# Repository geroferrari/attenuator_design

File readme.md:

Design a variable attenuator  from 0db to 30db  (steps of 1db) 

Max Frequency: 3GHz 

Max input Power: 0 dbm

Zin = Zout = 50 ohms.

Tools:
 - Jupyter notebooks
 - Qucs
 - Kicad
 
TO DO:
- finish design
- Assemble the pcb

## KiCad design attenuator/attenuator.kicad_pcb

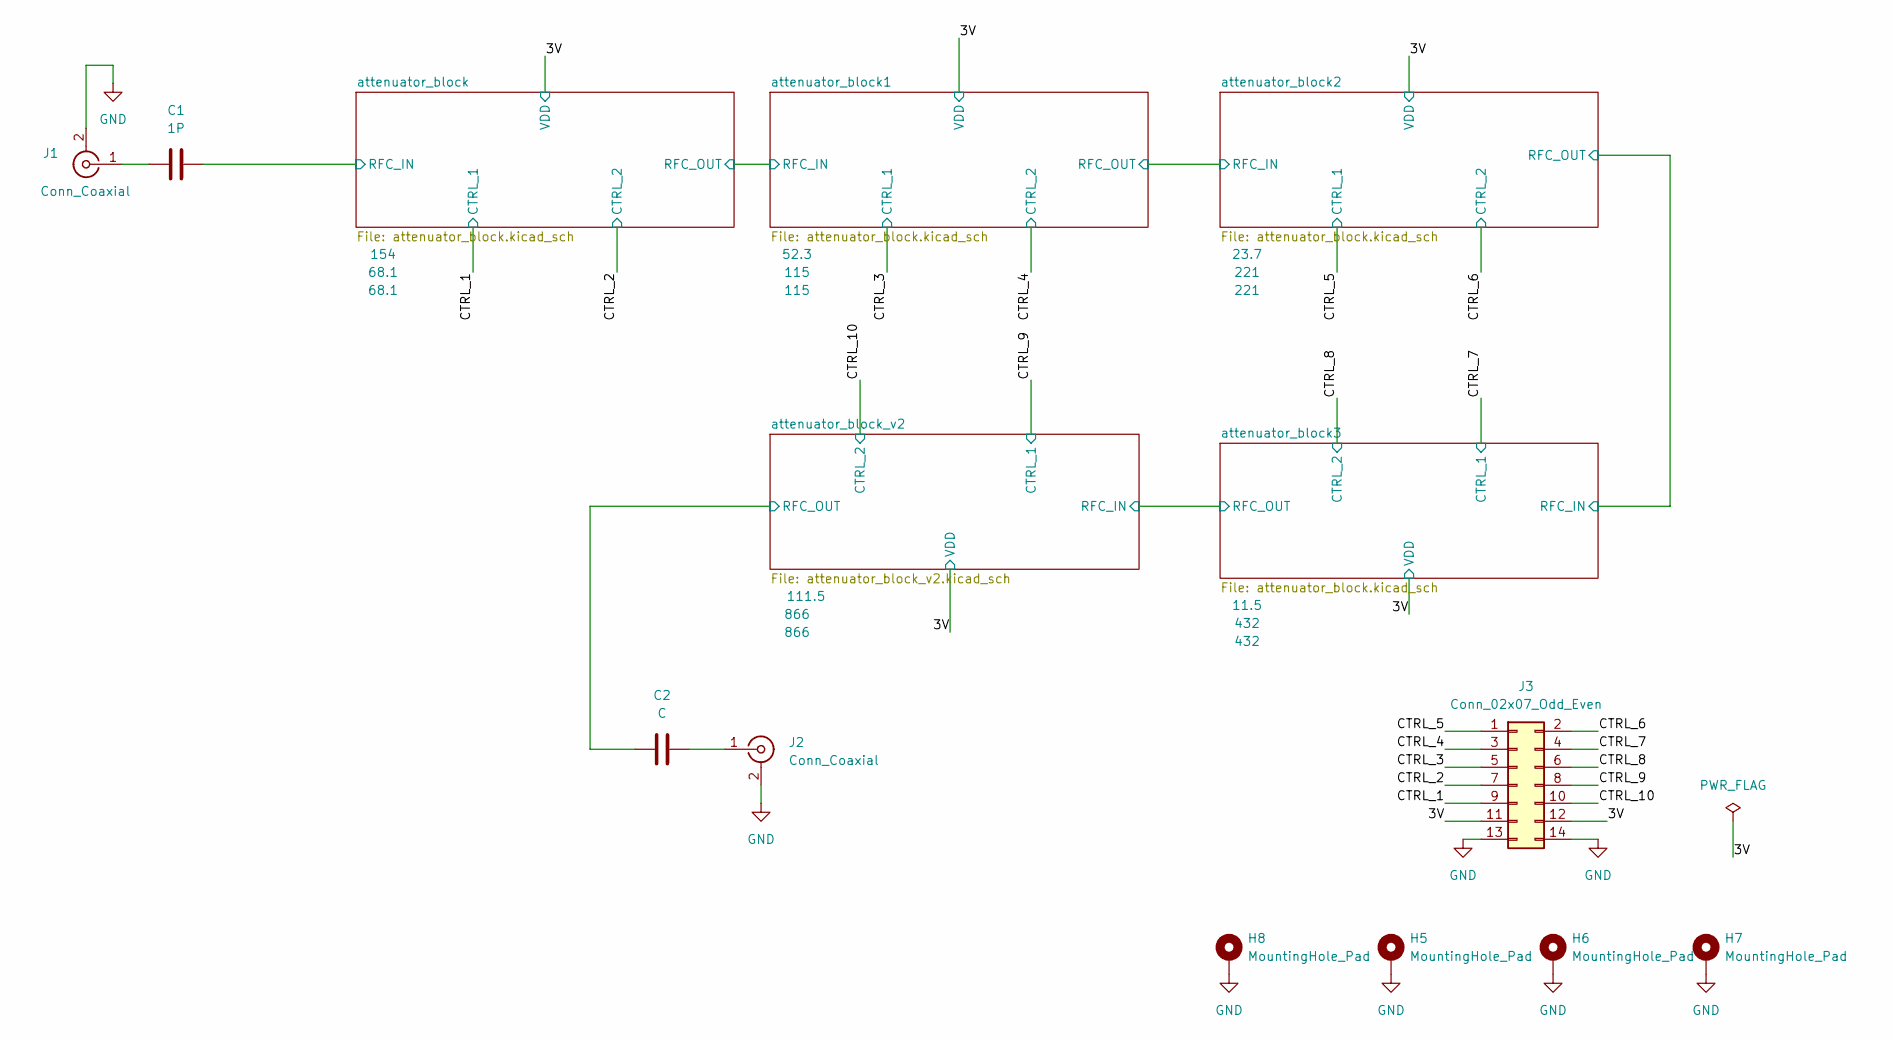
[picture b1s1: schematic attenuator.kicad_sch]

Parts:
C1: 1P; C_0603_1608Metric
C2: C; C_0603_1608Metric
H5, H6, H7, H8: MountingHole_Pad; MountingHole_3.2mm_M3_Pad_TopBottom
J1, J2: Conn_Coaxial; SMA_Amphenol_132289_EdgeMount
J3: Conn_02x07_Odd_Even; PinSocket_2x07_P1.27mm_Vertical

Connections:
/3V: J3.11, J3.12; also elsewhere on the board
/CTRL_1: J3.9; also elsewhere on the board
/CTRL_2: J3.7; also elsewhere on the board
/CTRL_3: J3.5; also elsewhere on the board
/CTRL_4: J3.3; also elsewhere on the board
/CTRL_5: J3.1; also elsewhere on the board
/CTRL_6: J3.2; also elsewhere on the board
/CTRL_7: J3.4; also elsewhere on the board
/CTRL_8: J3.6; also elsewhere on the board
/CTRL_9: J3.8; also elsewhere on the board
/CTRL_10: J3.10; also elsewhere on the board
/attenuator_block_v2/RFC_OUT: C2.1; also elsewhere on the board
GND: H5.1, H6.1, H7.1, H8.1, J1.2 (Ext), J2.2 (Ext), J3.13, J3.14; also elsewhere on the board
unnamed: C1.1, J1.1 (In)
unnamed: C2.2, J2.1 (In)

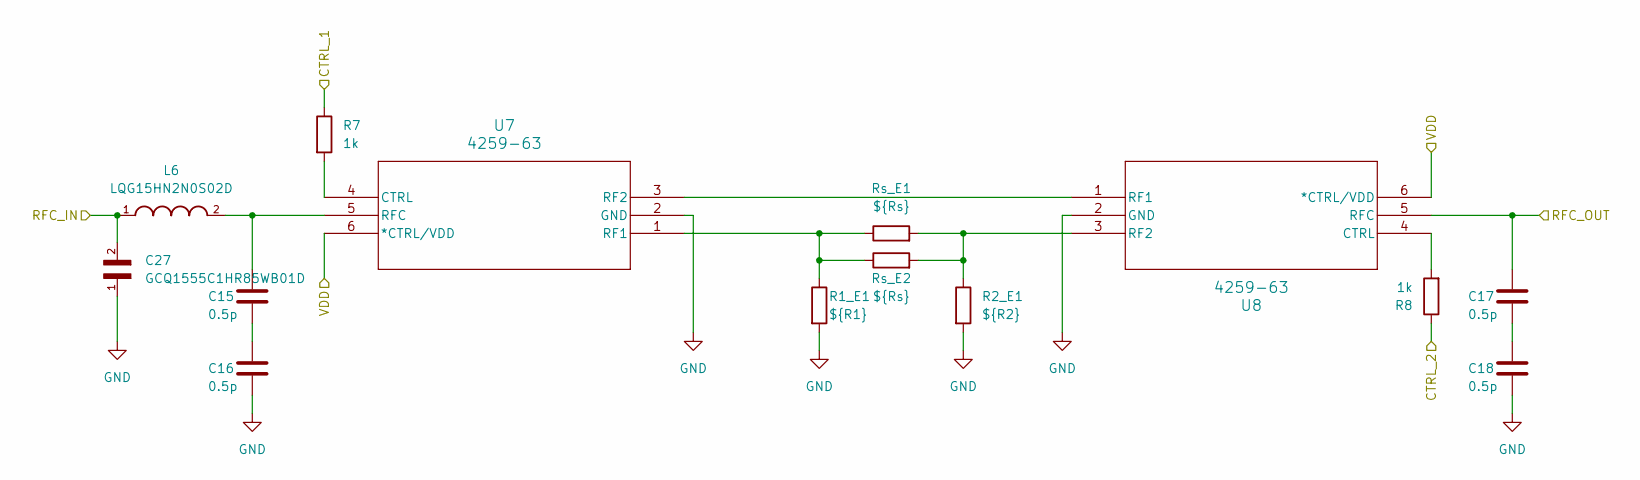
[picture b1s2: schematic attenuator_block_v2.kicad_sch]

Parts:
C15, C16, C17, C18: 0.5p; C_0603_1608Metric
C27: GCQ1555C1HR85WB01D; CAPC1005X55N
L6: LQG15HN2N0S02D; INDC1005X55N
R1_E1: ${R1}; R_0603_1608Metric_Pad0.98x0.95mm_HandSolder
R2_E1: ${R2}; R_0603_1608Metric_Pad0.98x0.95mm_HandSolder
R7, R8: 1k; R_0603_1608Metric_Pad0.98x0.95mm_HandSolder
Rs_E1, Rs_E2: ${Rs}; R_0603_1608Metric_Pad0.98x0.95mm_HandSolder
U7, U8: 4259-63; SC-70-6_PSM

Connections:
/3V: U7.6 (*CTRL/VDD), U8.6 (*CTRL/VDD); also elsewhere on the board
/CTRL_9: R7.1; also elsewhere on the board
/CTRL_10: R8.1; also elsewhere on the board
/attenuator_block3/RFC_OUT: C27.2, L6.1; also elsewhere on the board
/attenuator_block_v2/RFC_OUT: C17.1, U8.5 (RFC); also elsewhere on the board
GND: C16.2, C18.2, C27.1, R1_E1.2, R2_E1.2, U7.2 (GND), U8.2 (GND); also elsewhere on the board
unnamed: C15.2, C16.1
unnamed: C17.2, C18.1
unnamed: R7.2, U7.4 (CTRL)
unnamed: R1_E1.1, Rs_E1.1, Rs_E2.1, U7.1 (RF1)
unnamed: U7.3 (RF2), U8.1 (RF1)
unnamed: C15.1, L6.2, U7.5 (RFC)
unnamed: R8.2, U8.4 (CTRL)
unnamed: R2_E1.1, Rs_E1.2, Rs_E2.2, U8.3 (RF2)

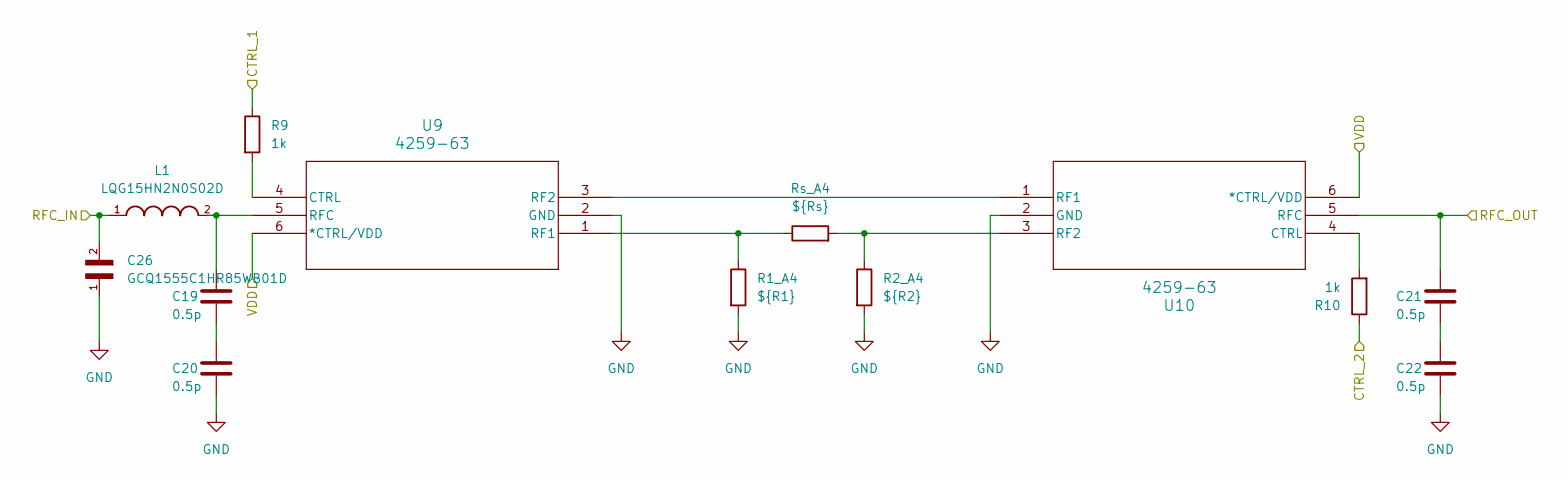
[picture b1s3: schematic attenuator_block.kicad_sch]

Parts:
C19, C20, C21, C22: 0.5p; C_0603_1608Metric
C26: GCQ1555C1HR85WB01D; CAPC1005X55N
L1: LQG15HN2N0S02D; INDC1005X55N
R1_A4: ${R1}; R_0603_1608Metric_Pad0.98x0.95mm_HandSolder
R2_A4: ${R2}; R_0603_1608Metric_Pad0.98x0.95mm_HandSolder
R9, R10: 1k; R_0603_1608Metric_Pad0.98x0.95mm_HandSolder
Rs_A4: ${Rs}; R_0603_1608Metric_Pad0.98x0.95mm_HandSolder
U9, U10: 4259-63; SC-70-6_PSM

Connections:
/3V: U9.6 (*CTRL/VDD), U10.6 (*CTRL/VDD); also elsewhere on the board
/CTRL_1: R9.1; also elsewhere on the board
/CTRL_2: R10.1; also elsewhere on the board
GND: C20.2, C22.2, C26.1, R1_A4.2, R2_A4.2, U9.2 (GND), U10.2 (GND); also elsewhere on the board
unnamed: C19.2, C20.1
unnamed: C21.2, C22.1
unnamed: R9.2, U9.4 (CTRL)
unnamed: R1_A4.1, Rs_A4.1, U9.1 (RF1)
unnamed: R10.2, U10.4 (CTRL)
unnamed: U9.3 (RF2), U10.1 (RF1)
unnamed: R2_A4.1, Rs_A4.2, U10.3 (RF2)

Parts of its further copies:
C3, C4, C5, C6, C7, C8, C9, C10, C11, C12, C13, C14: 0.5p; C_0603_1608Metric
C23, C24, C25: GCQ1555C1HR85WB01D; CAPC1005X55N
L2, L3, L4: LQG15HN2N0S02D; INDC1005X55N
R1, R2, R3, R4, R5, R6: 1k; R_0603_1608Metric_Pad0.98x0.95mm_HandSolder
U1, U2, U3, U4, U5, U6: 4259-63; SC-70-6_PSM

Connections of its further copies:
/3V: U1.6 (*CTRL/VDD), U2.6 (*CTRL/VDD), U3.6 (*CTRL/VDD), U4.6 (*CTRL/VDD), U5.6 (*CTRL/VDD), U6.6 (*CTRL/VDD); also elsewhere on the board
/CTRL_3: R1.1; also elsewhere on the board
/CTRL_4: R2.1; also elsewhere on the board
/CTRL_5: R3.1; also elsewhere on the board
/CTRL_6: R4.1; also elsewhere on the board
/CTRL_7: R5.1; also elsewhere on the board
/CTRL_8: R6.1; also elsewhere on the board
/attenuator_block1/RFC_OUT: C5.1, C24.2, L2.1, U2.5 (RFC)
/attenuator_block2/RFC_OUT: C9.1, C25.2, L3.1, U4.5 (RFC)
/attenuator_block3/RFC_OUT: C13.1, U6.5 (RFC); also elsewhere on the board
GND: C4.2, C6.2, C8.2, C10.2, C12.2, C14.2, C23.1, C24.1, C25.1, U1.2 (GND), U2.2 (GND), U3.2 (GND), U4.2 (GND), U5.2 (GND), U6.2 (GND); also elsewhere on the board
unnamed: C3.2, C4.1
unnamed: C5.2, C6.1
unnamed: C7.2, C8.1
unnamed: C9.2, C10.1
unnamed: C11.2, C12.1
unnamed: C13.2, C14.1
unnamed: R1.2, U1.4 (CTRL)
unnamed 29: U1.1 (RF1); also elsewhere on the board
unnamed: U1.3 (RF2), U2.1 (RF1)
unnamed: R2.2, U2.4 (CTRL)
unnamed 32: U2.3 (RF2); also elsewhere on the board
unnamed: R3.2, U3.4 (CTRL)
unnamed 34: U3.1 (RF1); also elsewhere on the board
unnamed: U3.3 (RF2), U4.1 (RF1)
unnamed: C7.1, L2.2, U3.5 (RFC)
unnamed: R4.2, U4.4 (CTRL)
unnamed 38: U4.3 (RF2); also elsewhere on the board
unnamed: R5.2, U5.4 (CTRL)
unnamed 40: U5.1 (RF1); also elsewhere on the board
unnamed: U5.3 (RF2), U6.1 (RF1)
unnamed: C11.1, L3.2, U5.5 (RFC)
unnamed: R6.2, U6.4 (CTRL)
unnamed 44: U6.3 (RF2); also elsewhere on the board

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
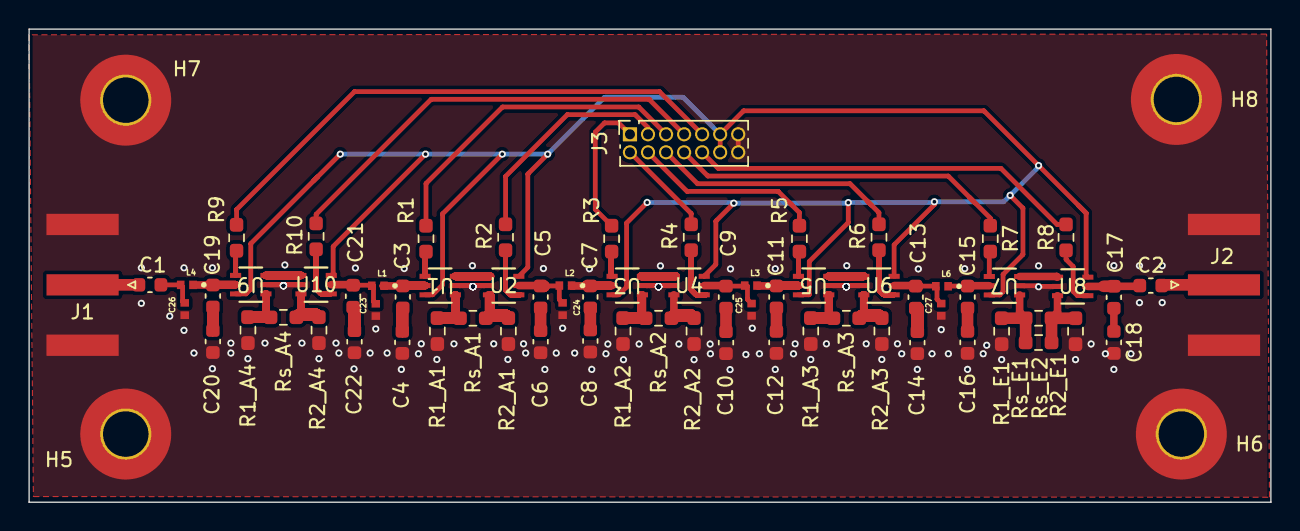
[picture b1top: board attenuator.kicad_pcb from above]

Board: 2 copper layers, 87.4 x 33.3 mm, 75 parts (0 on the bottom side), 60 nets.

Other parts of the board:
R1_A1, R2_A1: 115; R_0603_1608Metric_Pad0.98x0.95mm_HandSolder
R1_A2, R2_A2: 221; R_0603_1608Metric_Pad0.98x0.95mm_HandSolder
R1_A3, R2_A3: 432; R_0603_1608Metric_Pad0.98x0.95mm_HandSolder
Rs_A1: 52.3; R_0603_1608Metric_Pad0.98x0.95mm_HandSolder
Rs_A2: 23.7; R_0603_1608Metric_Pad0.98x0.95mm_HandSolder
Rs_A3: 11.5; R_0603_1608Metric_Pad0.98x0.95mm_HandSolder

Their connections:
GND: R1_A1.2, R1_A2.2, R1_A3.2, R2_A1.2, R2_A2.2, R2_A3.2; also elsewhere on the board
unnamed 29: R1_A1.1, Rs_A1.1; also elsewhere on the board
unnamed 32: R2_A1.1, Rs_A1.2; also elsewhere on the board
unnamed 34: R1_A2.1, Rs_A2.1; also elsewhere on the board
unnamed 38: R2_A2.1, Rs_A2.2; also elsewhere on the board
unnamed 40: R1_A3.1, Rs_A3.1; also elsewhere on the board
unnamed 44: R2_A3.1, Rs_A3.2; also elsewhere on the board

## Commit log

2023-12-27 first item done
2023-12-27 add missing images
2023-12-28 add qucs schematic
2024-01-02 kicad design
2024-01-03 change hierarchical sheets
2024-01-03 pcb improve it
2024-01-03 minnor changes in pcb
2024-01-05 translate it to english, update notes
2024-01-05 add qucs simulations
2024-01-06 finish simulation and kicad
